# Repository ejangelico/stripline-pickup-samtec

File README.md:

# stripline-pickup-samtec
This is a KiCad project for designing a strip-line pickup with samtec connectors for capacitively coupled LAPPD

# libraries and footprints
I've created a library called stripline-pickup-samtec.pretty to hold all custom footprints. Make sure to import/add this library to the project if it does not show up on first load. Please add all footprints that the board depends on to this library so that this repository is stand-alone. Footprint files may be saved in the "footprints" folder.

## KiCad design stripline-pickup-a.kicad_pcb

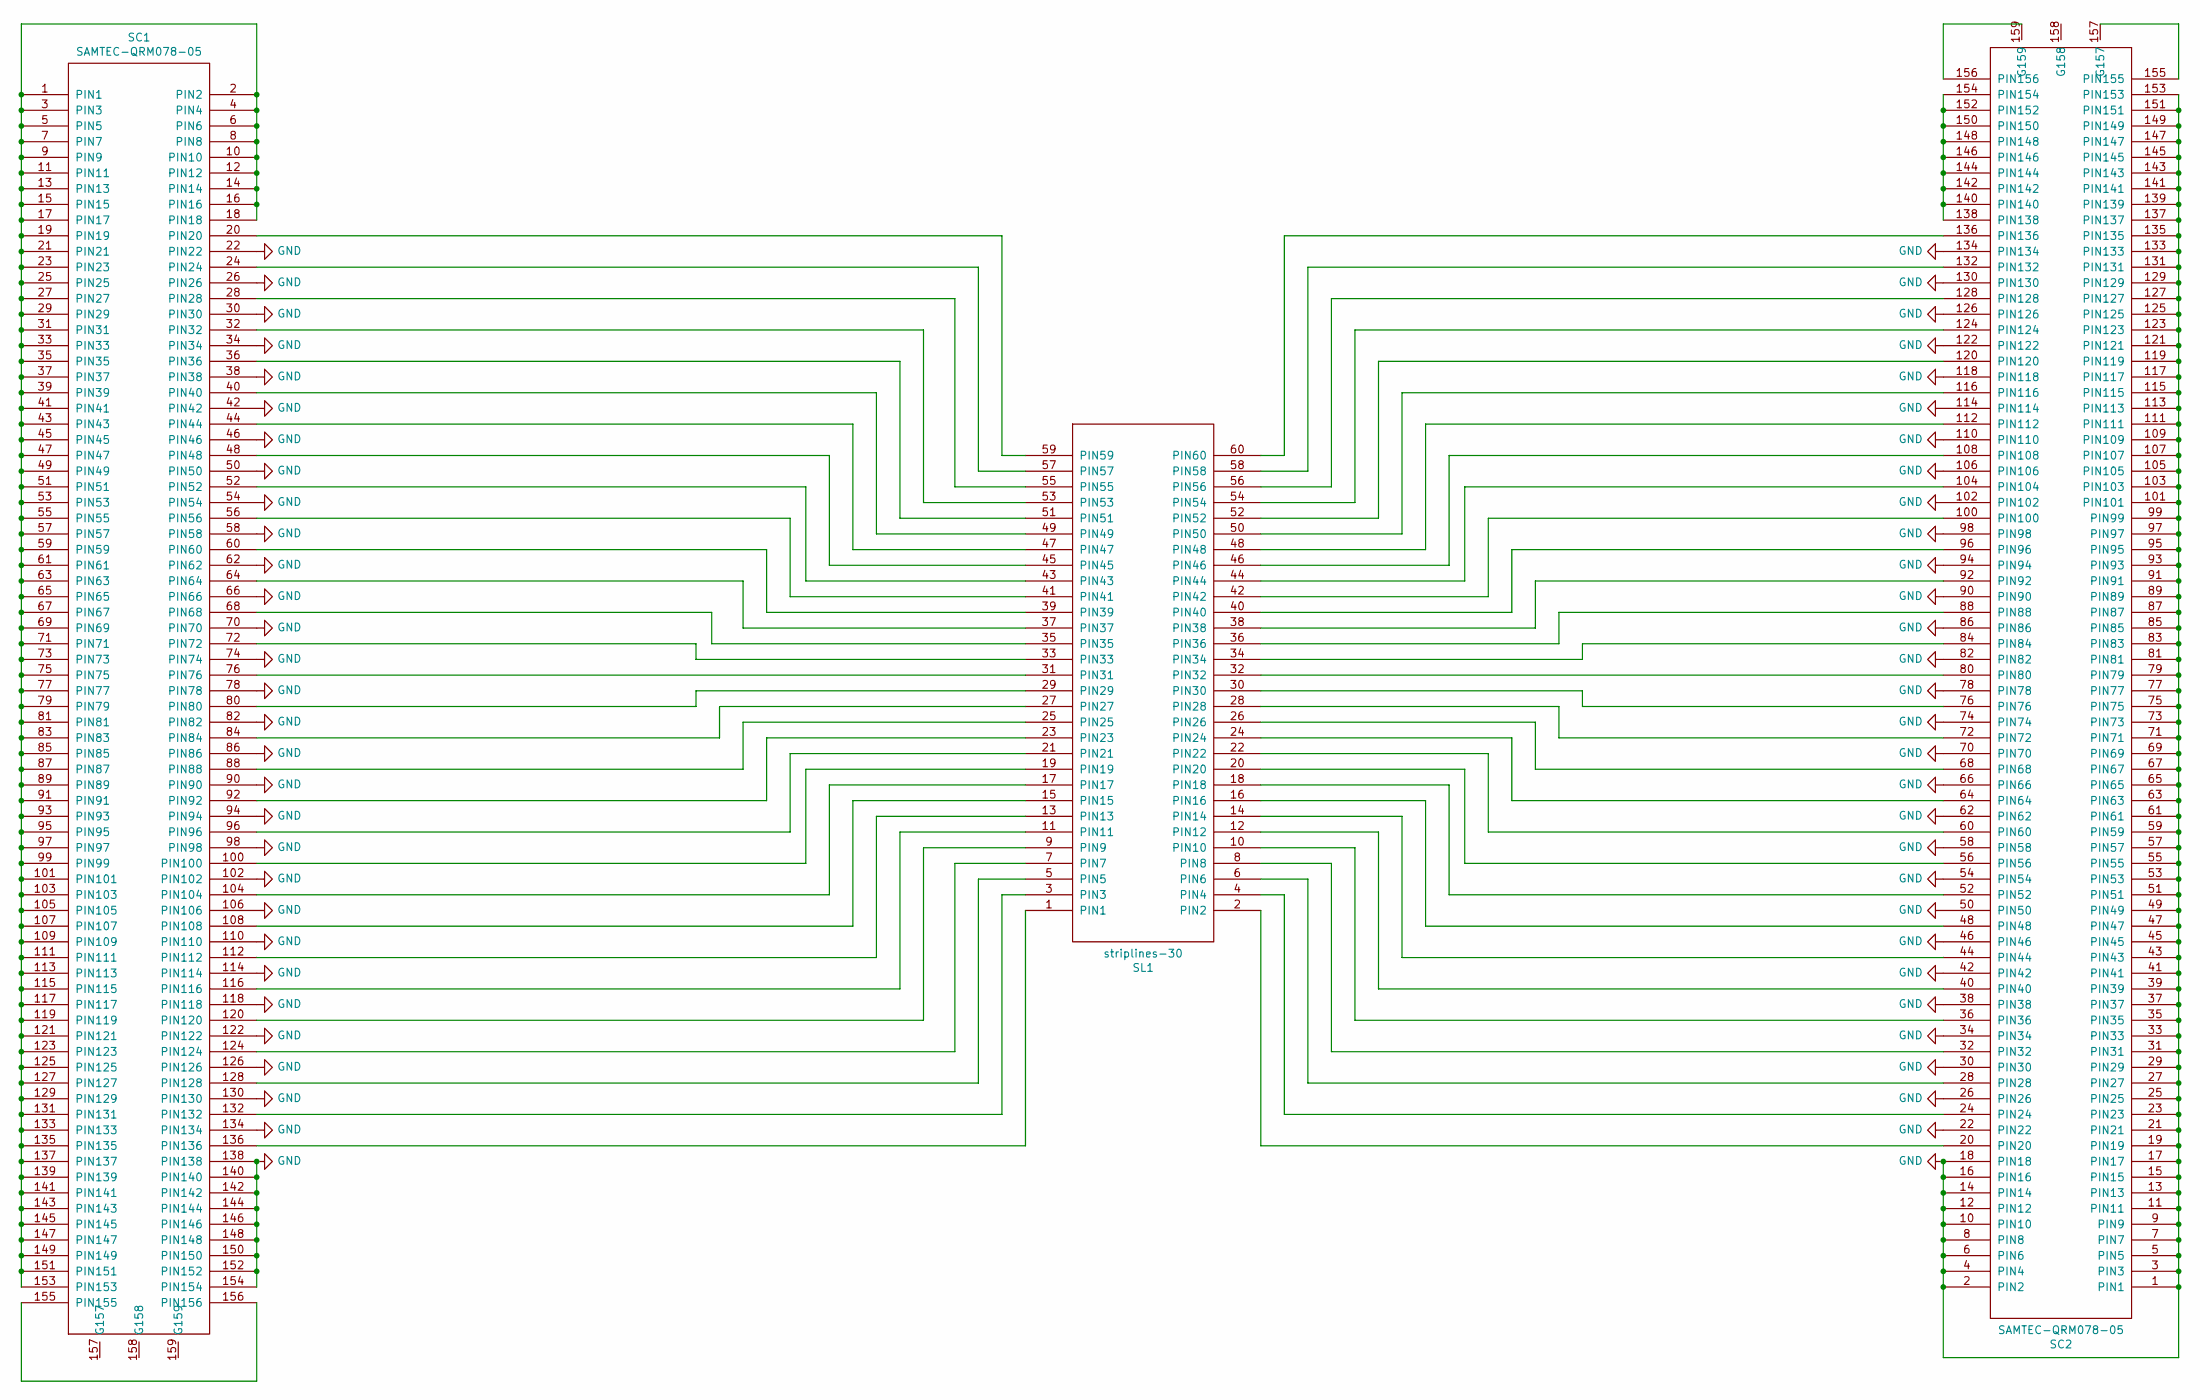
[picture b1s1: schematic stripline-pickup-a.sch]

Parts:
SC1, SC2: SAMTEC-QRM078-05; QRM8-078-05-grounded
SL1: striplines-30; strips-n30-50ohm-9milprepreg

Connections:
GND: SC1.22 (PIN22), SC1.26 (PIN26), SC1.30 (PIN30), SC1.34 (PIN34), SC1.38 (PIN38), SC1.42 (PIN42), SC1.46 (PIN46), SC1.50 (PIN50), SC1.54 (PIN54), SC1.58 (PIN58), SC1.62 (PIN62), SC1.66 (PIN66), SC1.70 (PIN70), SC1.74 (PIN74), SC1.78 (PIN78), SC1.82 (PIN82), SC1.86 (PIN86), SC1.90 (PIN90), SC1.94 (PIN94), SC1.98 (PIN98), SC1.102 (PIN102), SC1.106 (PIN106), SC1.110 (PIN110), SC1.114 (PIN114), SC1.118 (PIN118), SC1.122 (PIN122), SC1.126 (PIN126), SC1.130 (PIN130), SC1.134 (PIN134), SC1.138 (PIN138), SC1.140 (PIN140), SC1.142 (PIN142), SC1.144 (PIN144), SC1.146 (PIN146), SC1.148 (PIN148), SC1.150 (PIN150), SC1.152 (PIN152), SC1.154 (PIN154), SC2.1 (PIN1), SC2.2 (PIN2), SC2.3 (PIN3), SC2.4 (PIN4), SC2.5 (PIN5), SC2.6 (PIN6), SC2.7 (PIN7), SC2.8 (PIN8), SC2.9 (PIN9), SC2.10 (PIN10), SC2.11 (PIN11), SC2.12 (PIN12), SC2.13 (PIN13), SC2.14 (PIN14), SC2.15 (PIN15), SC2.16 (PIN16), SC2.17 (PIN17), SC2.18 (PIN18), SC2.19 (PIN19), SC2.21 (PIN21), SC2.22 (PIN22), SC2.23 (PIN23), SC2.25 (PIN25), SC2.26 (PIN26), SC2.27 (PIN27), SC2.29 (PIN29), SC2.30 (PIN30), SC2.31 (PIN31), SC2.33 (PIN33), SC2.34 (PIN34), SC2.35 (PIN35), SC2.37 (PIN37), SC2.38 (PIN38), SC2.39 (PIN39), SC2.41 (PIN41), SC2.42 (PIN42), SC2.43 (PIN43), SC2.45 (PIN45), SC2.46 (PIN46), SC2.47 (PIN47), SC2.49 (PIN49), SC2.50 (PIN50), SC2.51 (PIN51), SC2.53 (PIN53), SC2.54 (PIN54), SC2.55 (PIN55), SC2.57 (PIN57), SC2.58 (PIN58), SC2.59 (PIN59), SC2.61 (PIN61), SC2.62 (PIN62), SC2.63 (PIN63), SC2.65 (PIN65), SC2.66 (PIN66), SC2.67 (PIN67), SC2.69 (PIN69), SC2.70 (PIN70), SC2.71 (PIN71), SC2.73 (PIN73), SC2.74 (PIN74), SC2.75 (PIN75), SC2.77 (PIN77), SC2.78 (PIN78), SC2.79 (PIN79), SC2.81 (PIN81), SC2.82 (PIN82), SC2.83 (PIN83), SC2.85 (PIN85), SC2.86 (PIN86), SC2.87 (PIN87), SC2.89 (PIN89), SC2.90 (PIN90), SC2.91 (PIN91), SC2.93 (PIN93), SC2.94 (PIN94), SC2.95 (PIN95), SC2.97 (PIN97), SC2.98 (PIN98), SC2.99 (PIN99), SC2.101 (PIN101), SC2.102 (PIN102), SC2.103 (PIN103), SC2.105 (PIN105), SC2.106 (PIN106), SC2.107 (PIN107), SC2.109 (PIN109), SC2.110 (PIN110), SC2.111 (PIN111), SC2.113 (PIN113), SC2.114 (PIN114), SC2.115 (PIN115), SC2.117 (PIN117), SC2.118 (PIN118), SC2.119 (PIN119), SC2.121 (PIN121), SC2.122 (PIN122), SC2.123 (PIN123), SC2.125 (PIN125), SC2.126 (PIN126), SC2.127 (PIN127), SC2.129 (PIN129), SC2.130 (PIN130), SC2.131 (PIN131), SC2.133 (PIN133), SC2.134 (PIN134), SC2.135 (PIN135), SC2.137 (PIN137), SC2.139 (PIN139), SC2.141 (PIN141), SC2.143 (PIN143), SC2.145 (PIN145), SC2.147 (PIN147), SC2.149 (PIN149), SC2.151 (PIN151), SC2.153 (PIN153)
unnamed: SC1.1 (PIN1), SC1.2 (PIN2), SC1.3 (PIN3), SC1.4 (PIN4), SC1.5 (PIN5), SC1.6 (PIN6), SC1.7 (PIN7), SC1.8 (PIN8), SC1.9 (PIN9), SC1.10 (PIN10), SC1.11 (PIN11), SC1.12 (PIN12), SC1.13 (PIN13), SC1.14 (PIN14), SC1.15 (PIN15), SC1.16 (PIN16), SC1.17 (PIN17), SC1.18 (PIN18), SC1.19 (PIN19), SC1.21 (PIN21), SC1.23 (PIN23), SC1.25 (PIN25), SC1.27 (PIN27), SC1.29 (PIN29), SC1.31 (PIN31), SC1.33 (PIN33), SC1.35 (PIN35), SC1.37 (PIN37), SC1.39 (PIN39), SC1.41 (PIN41), SC1.43 (PIN43), SC1.45 (PIN45), SC1.47 (PIN47), SC1.49 (PIN49), SC1.51 (PIN51), SC1.53 (PIN53), SC1.55 (PIN55), SC1.57 (PIN57), SC1.59 (PIN59), SC1.61 (PIN61), SC1.63 (PIN63), SC1.65 (PIN65), SC1.67 (PIN67), SC1.69 (PIN69), SC1.71 (PIN71), SC1.73 (PIN73), SC1.75 (PIN75), SC1.77 (PIN77), SC1.79 (PIN79), SC1.81 (PIN81), SC1.83 (PIN83), SC1.85 (PIN85), SC1.87 (PIN87), SC1.89 (PIN89), SC1.91 (PIN91), SC1.93 (PIN93), SC1.95 (PIN95), SC1.97 (PIN97), SC1.99 (PIN99), SC1.101 (PIN101), SC1.103 (PIN103), SC1.105 (PIN105), SC1.107 (PIN107), SC1.109 (PIN109), SC1.111 (PIN111), SC1.113 (PIN113), SC1.115 (PIN115), SC1.117 (PIN117), SC1.119 (PIN119), SC1.121 (PIN121), SC1.123 (PIN123), SC1.125 (PIN125), SC1.127 (PIN127), SC1.129 (PIN129), SC1.131 (PIN131), SC1.133 (PIN133), SC1.135 (PIN135), SC1.137 (PIN137), SC1.139 (PIN139), SC1.141 (PIN141), SC1.143 (PIN143), SC1.145 (PIN145), SC1.147 (PIN147), SC1.149 (PIN149), SC1.151 (PIN151), SC1.153 (PIN153)
unnamed: SC1.20 (PIN20), SL1.59 (PIN59)
unnamed: SC1.24 (PIN24), SL1.57 (PIN57)
unnamed: SC1.28 (PIN28), SL1.55 (PIN55)
unnamed: SC1.32 (PIN32), SL1.53 (PIN53)
unnamed: SC1.36 (PIN36), SL1.51 (PIN51)
unnamed: SC1.40 (PIN40), SL1.49 (PIN49)
unnamed: SC1.44 (PIN44), SL1.47 (PIN47)
unnamed: SC1.48 (PIN48), SL1.45 (PIN45)
unnamed: SC1.52 (PIN52), SL1.43 (PIN43)
unnamed: SC1.56 (PIN56), SL1.41 (PIN41)
unnamed: SC1.60 (PIN60), SL1.39 (PIN39)
unnamed: SC1.64 (PIN64), SL1.37 (PIN37)
unnamed: SC1.68 (PIN68), SL1.35 (PIN35)
unnamed: SC1.72 (PIN72), SL1.33 (PIN33)
unnamed: SC1.76 (PIN76), SL1.31 (PIN31)
unnamed: SC1.80 (PIN80), SL1.29 (PIN29)
unnamed: SC1.84 (PIN84), SL1.27 (PIN27)
unnamed: SC1.88 (PIN88), SL1.25 (PIN25)
unnamed: SC1.92 (PIN92), SL1.23 (PIN23)
unnamed: SC1.96 (PIN96), SL1.21 (PIN21)
unnamed: SC1.100 (PIN100), SL1.19 (PIN19)
unnamed: SC1.104 (PIN104), SL1.17 (PIN17)
unnamed: SC1.108 (PIN108), SL1.15 (PIN15)
unnamed: SC1.112 (PIN112), SL1.13 (PIN13)
unnamed: SC1.116 (PIN116), SL1.11 (PIN11)
unnamed: SC1.120 (PIN120), SL1.9 (PIN9)
unnamed: SC1.124 (PIN124), SL1.7 (PIN7)
unnamed: SC1.128 (PIN128), SL1.5 (PIN5)
unnamed: SC1.132 (PIN132), SL1.3 (PIN3)
unnamed: SC1.136 (PIN136), SL1.1 (PIN1)
unnamed: SC1.155 (PIN155), SC1.156 (PIN156)
unnamed: SC2.20 (PIN20), SL1.2 (PIN2)
unnamed: SC2.24 (PIN24), SL1.4 (PIN4)
unnamed: SC2.28 (PIN28), SL1.6 (PIN6)
unnamed: SC2.32 (PIN32), SL1.8 (PIN8)
unnamed: SC2.36 (PIN36), SL1.10 (PIN10)
unnamed: SC2.40 (PIN40), SL1.12 (PIN12)
unnamed: SC2.44 (PIN44), SL1.14 (PIN14)
unnamed: SC2.48 (PIN48), SL1.16 (PIN16)
unnamed: SC2.52 (PIN52), SL1.18 (PIN18)
unnamed: SC2.56 (PIN56), SL1.20 (PIN20)
unnamed: SC2.60 (PIN60), SL1.22 (PIN22)
unnamed: SC2.64 (PIN64), SL1.24 (PIN24)
unnamed: SC2.68 (PIN68), SL1.26 (PIN26)
unnamed: SC2.72 (PIN72), SL1.28 (PIN28)
unnamed: SC2.76 (PIN76), SL1.30 (PIN30)
unnamed: SC2.80 (PIN80), SL1.32 (PIN32)
unnamed: SC2.84 (PIN84), SL1.34 (PIN34)
unnamed: SC2.88 (PIN88), SL1.36 (PIN36)
unnamed: SC2.92 (PIN92), SL1.38 (PIN38)
unnamed: SC2.96 (PIN96), SL1.40 (PIN40)
unnamed: SC2.100 (PIN100), SL1.42 (PIN42)
unnamed: SC2.104 (PIN104), SL1.44 (PIN44)
unnamed: SC2.108 (PIN108), SL1.46 (PIN46)
unnamed: SC2.112 (PIN112), SL1.48 (PIN48)
unnamed: SC2.116 (PIN116), SL1.50 (PIN50)
unnamed: SC2.120 (PIN120), SL1.52 (PIN52)
unnamed: SC2.124 (PIN124), SL1.54 (PIN54)
unnamed: SC2.128 (PIN128), SL1.56 (PIN56)
unnamed: SC2.132 (PIN132), SL1.58 (PIN58)
unnamed: SC2.136 (PIN136), SL1.60 (PIN60)
unnamed: SC2.138 (PIN138), SC2.140 (PIN140), SC2.142 (PIN142), SC2.144 (PIN144), SC2.146 (PIN146), SC2.148 (PIN148), SC2.150 (PIN150), SC2.152 (PIN152), SC2.154 (PIN154)
unnamed: SC2.155 (PIN155), SC2.157 (G157)
unnamed: SC2.156 (PIN156), SC2.159 (G159)

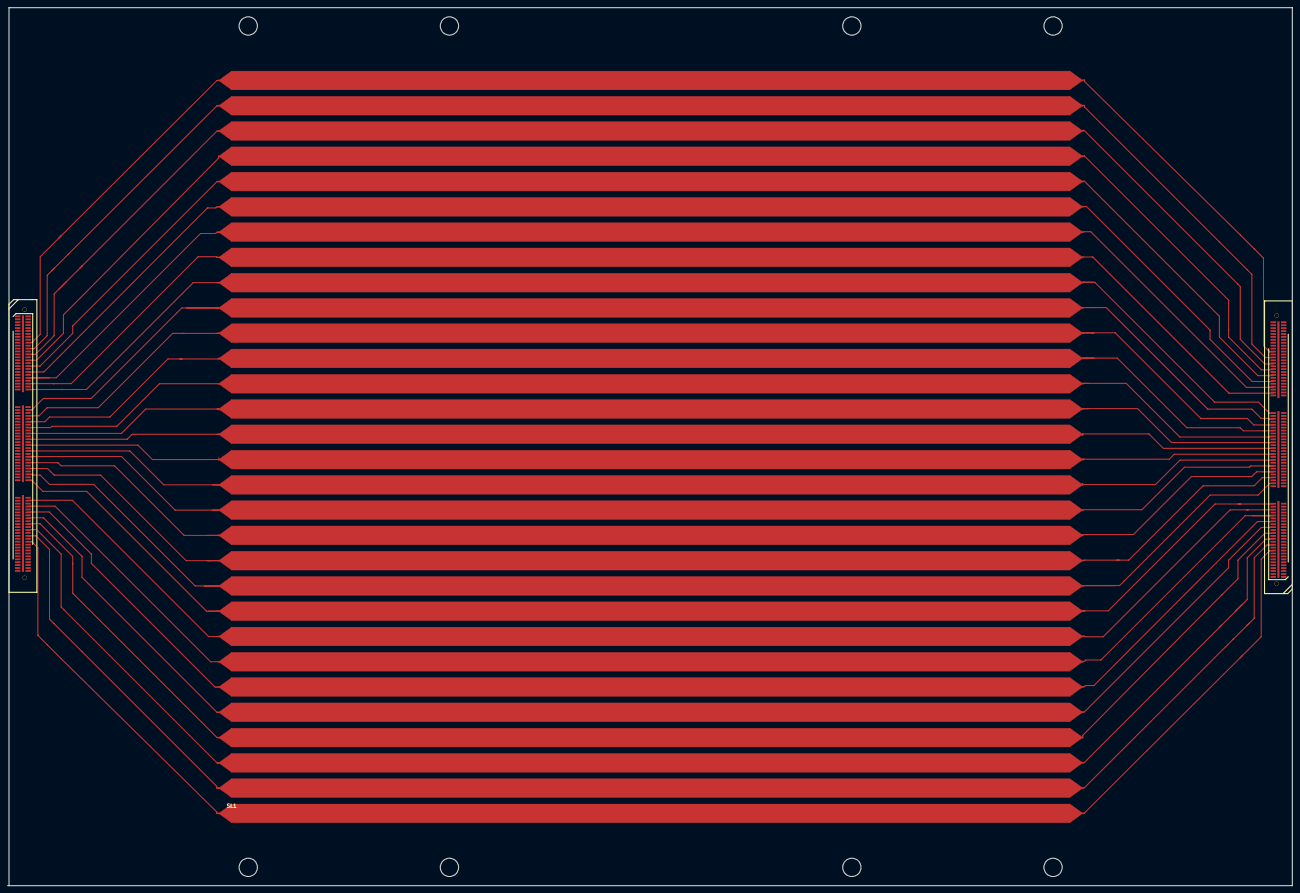
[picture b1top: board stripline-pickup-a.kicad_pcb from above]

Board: 4 copper layers, 351.2 x 240.0 mm, 3 parts (0 on the bottom side), 66 nets.

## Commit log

2020-03-10 First commit to a draft version of the pickup. This includes a stripline footprint that needs changing, half a side of routing to samtec connectors on the top layer, two separate ground planes for th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
2020-03-16 samtec footprinted modified to be through hole
2020-03-16 stripline width modified and routed to samtec connectors.
